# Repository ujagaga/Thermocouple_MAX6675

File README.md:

"# Thermocouple_MAX6675" 

Firmware, Schematic and PCB for thermostat using thermocouple module with probe. 
The intent is to provide regulation of a heater in temperature range from 250 to 400 degrees celsius.
There are 5 LED's for indicating target temperature. When the target is 200, the first LED is ON.
When it is 225, LEDs 1 and 2 are on. At 250, onlu LED 2 is ON and so on...

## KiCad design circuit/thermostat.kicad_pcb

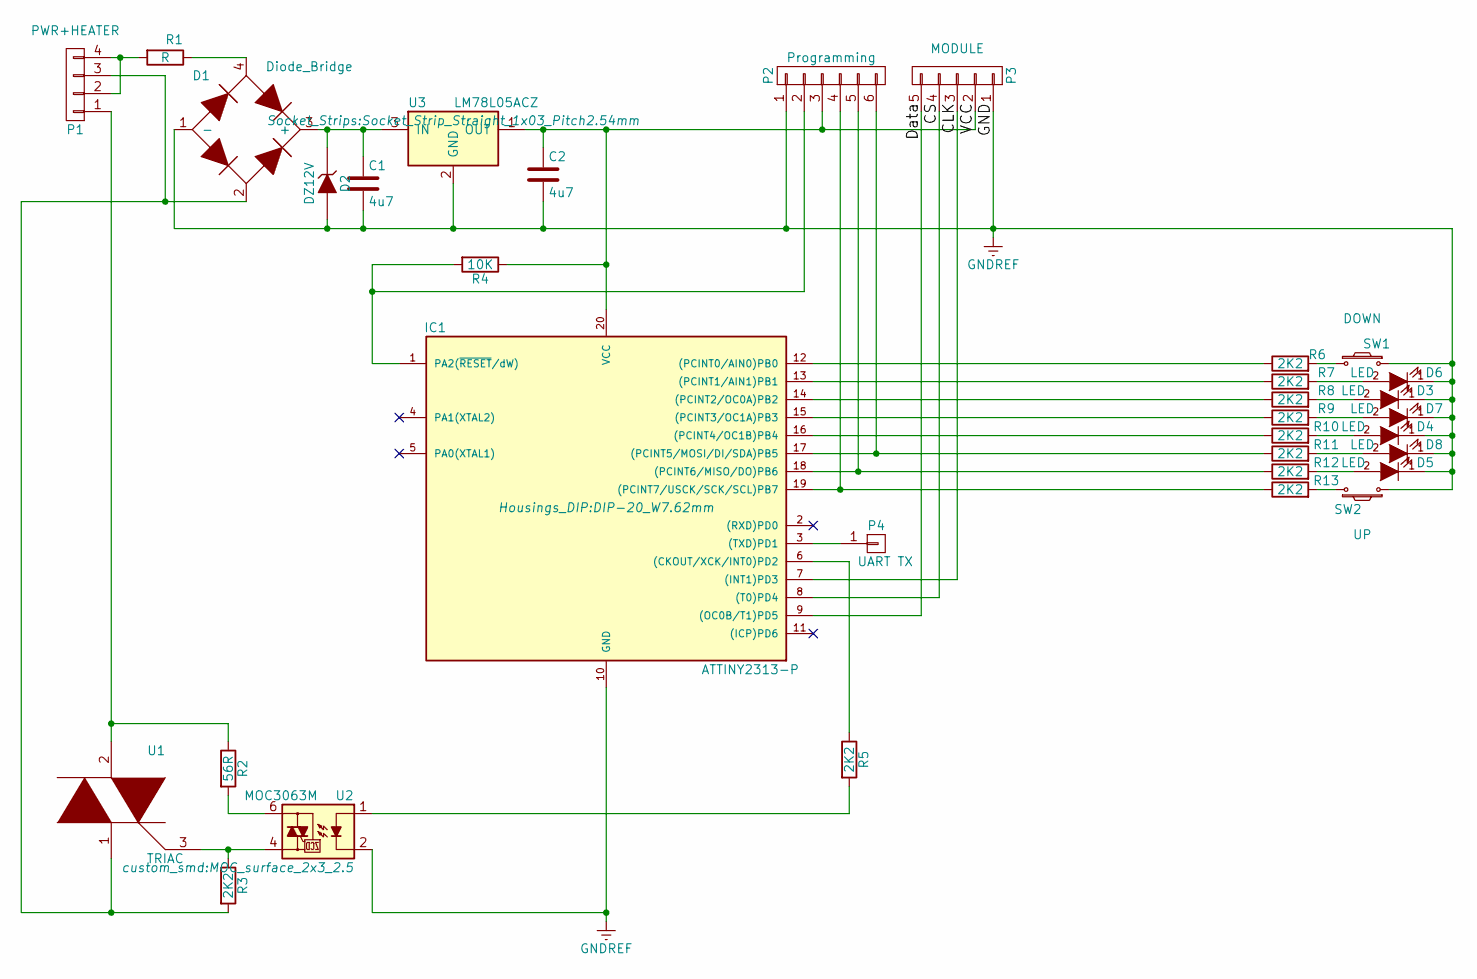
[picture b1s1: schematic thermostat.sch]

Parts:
C1, C2: 4u7; C_0805_HandSoldering
D1: Diode_Bridge; GREC_surface_2x2
D2: DZ12V; D_T-1_P5.08mm_Horizontal
D3, D4, D5, D6, D7, D8: LED; Socket_Strip_Straight_1x02_Pitch2.54mm
IC1: ATTINY2313-P; DIP-20_W7.62mm
P1: PWR+HEATER; Socket_Strip_Angled_1x04_Pitch2.54mm
P2: Programming; Socket_Strip_Straight_1x06_Pitch2.54mm
P3: MODULE; Socket_Strip_Angled_1x05_Pitch2.54mm
P4: UART TX; Socket_Strip_Straight_1x01_Pitch2.54mm
R1: R; R_Axial_DIN0204_L3.6mm_D1.6mm_P7.62mm_Horizontal
R2: 56R; R_0805_HandSoldering
R3, R5, R6, R7, R8, R9, R10, R11, R12, R13: 2K2; R_0805_HandSoldering
R4: 10K; R_0805_HandSoldering
SW1: DOWN; Micro_sw_1
SW2: UP; Micro_sw_1
U1: TRIAC; Socket_Strip_Angled_1x03_Pitch2.54mm
U2: MOC3063M; MOC_surface_2x3_2.5
U3: LM78L05ACZ; Socket_Strip_Straight_1x03_Pitch2.54mm

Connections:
GNDREF: C1.2, C2.2, D1.1 (-), D2.2 (A), D3.1 (K), D4.1 (K), D5.1 (K), D6.1 (K), D7.1 (K), D8.1 (K), IC1.10 (GND), P2.1, P3.1, SW1.2, SW2.1, U2.2, U3.2 (GND)
unnamed: C1.1, D1.3 (+), D2.1 (K), U3.3 (IN)
unnamed: C2.1, IC1.20 (VCC), P2.3, P3.2, R4.1, U3.1 (OUT)
unnamed: D1.2, P1.3, R3.2, U1.1
unnamed: D1.4, R1.1
unnamed: D3.2 (A), R8.2
unnamed: D4.2 (A), R10.2
unnamed: D5.2 (A), R12.2
unnamed: D6.2 (A), R7.2
unnamed: D7.2 (A), R9.2
unnamed: D8.2 (A), R11.2
unnamed: IC1.1 (PA2(~RESET~/dW)), P2.2, R4.2
unnamed: IC1.3 ((TXD)PD1), P4.1
unnamed: IC1.6 ((CKOUT/XCK/INT0)PD2), R5.1
unnamed: IC1.7 ((INT1)PD3), P3.3
unnamed: IC1.8 ((T0)PD4), P3.4
unnamed: IC1.9 ((OC0B/T1)PD5), P3.5
unnamed: IC1.12 ((PCINT0/AIN0)PB0), R6.1
unnamed: IC1.13 ((PCINT1/AIN1)PB1), R7.1
unnamed: IC1.14 ((PCINT2/OC0A)PB2), R8.1
unnamed: IC1.15 ((PCINT3/OC1A)PB3), R9.1
unnamed: IC1.16 ((PCINT4/OC1B)PB4), R10.1
unnamed: IC1.17 ((PCINT5/MOSI/DI/SDA)PB5), P2.6, R11.1
unnamed: IC1.18 ((PCINT6/MISO/DO)PB6), P2.5, R12.1
unnamed: IC1.19 ((PCINT7/USCK/SCK/SCL)PB7), P2.4, R13.1
unnamed: P1.1, R2.1, U1.2
unnamed: P1.2, P1.4, R1.2
unnamed: R2.2, U2.6
unnamed: R3.1, U1.3, U2.4
unnamed: R5.2, U2.1
unnamed: R6.2, SW1.1
unnamed: R13.2, SW2.2

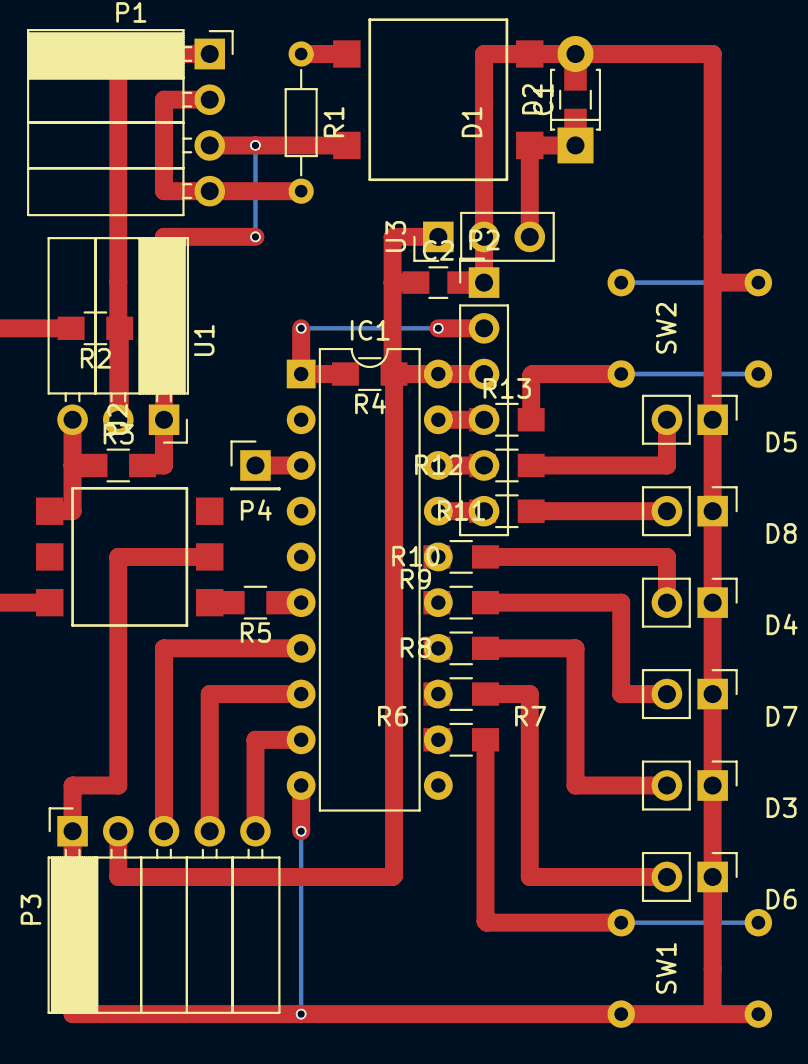
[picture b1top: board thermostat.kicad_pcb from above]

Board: 2 copper layers, 33 parts (0 on the bottom side), 32 nets.

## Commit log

2017-03-09 in progress
2017-03-09 Still in progress
2017-03-09 Finished schematic
2017-03-09 More adjustments to pcb
2017-03-10 Corrected sch and pcb
2017-03-10 Finished the FW
2017-03-10 PCB reduced
2018-10-19 New concept
2018-10-28 Switched to ATmega168
2018-10-28 Finished first code version
